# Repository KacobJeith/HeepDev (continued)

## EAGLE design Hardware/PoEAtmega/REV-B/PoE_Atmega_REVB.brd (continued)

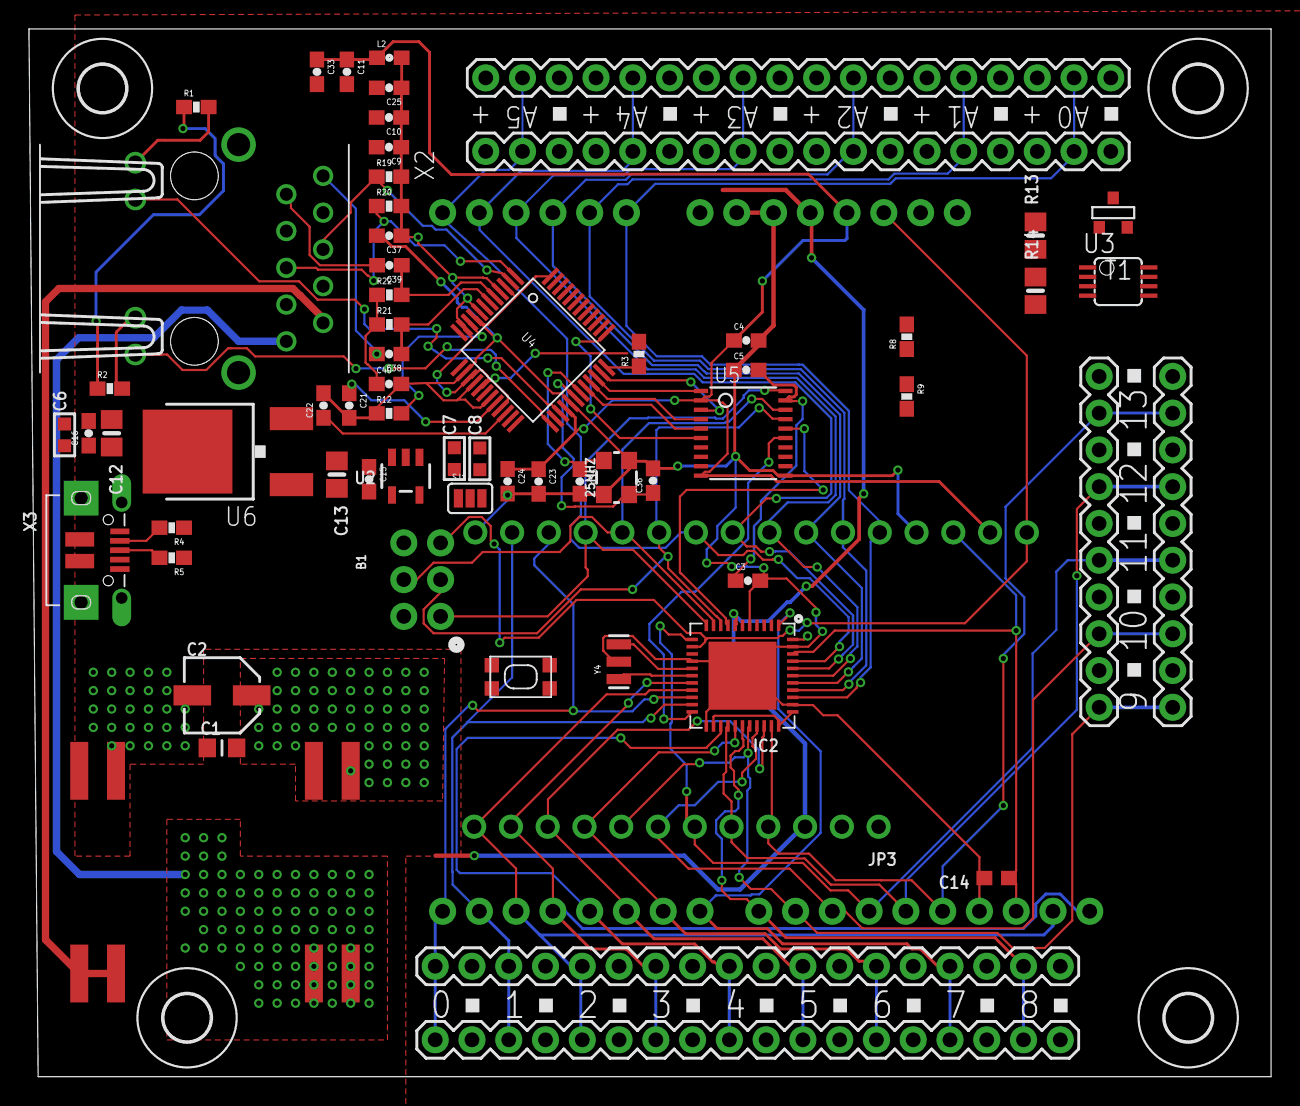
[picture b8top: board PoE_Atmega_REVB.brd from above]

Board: 2 copper layers, 85.8 x 72.4 mm, 70 parts (1 on the bottom side), 66 nets.

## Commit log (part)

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2018-04-10 HEEP-953 added the icons and canonical link to redirect http to https
2018-04-10 HEEP-952 dynamically import the landing page, reduces the critical loading path resource size by factor of 2
2018-04-10 HEEP-952 trying out some new babel modules to try to get dynamic importing to work
2018-04-10 HEEP-964 added logo
2018-04-10 HEEP-954 Landing, Store, and Checkout routes converted to lazy-loads. Some are unnecessary, but provide good example of how webpack and the browser work together to optimize resources
2018-04-10 HEEP-964 changed the way the logo loads in mobile vs. standard
2018-04-11 HEEP-964 fixed logo centering
2018-04-12 HEEP-949 updated to RS-274X (proper format for allpcb)
2018-04-12 HEEP-952 import specific icons instead of entire library
2018-04-12 HEEP-965 added gsap to package
2018-04-12 HEEP-951 fixed encoding issue when converting strings back into byte arrays. Wifi Reset works now
2018-04-13 HEEP-807 Only send the outputs
2018-04-13 HEEP-925 Added specifier to determine if WiFi
2018-04-13 HEEP-925 Calculate core memory correctly
2018-04-13 HEEP-927 upgrade .babelrc to the same that website is using, and remove unused npm modules
2018-04-13 HEEP-807 Added extra functions to express the many different ways to set a command and send data
2018-04-13 HEEP-960 use SVG for heep logo. Also adding missing svg for website
2018-04-13 HEEP-927 editing other pointers to assets to use the src/ path, and bringing back HMR on the dev server
2018-04-13 HEEP-963 the browser seems to have a cap on file size to store in localStorage, so at the moment the vendors bundle is not saving, but now that we understand how this works we are getting close
2018-04-16 HEEP-927 bump the electron version number
2018-04-16 HEEP-939 fixed reducer lazy loading for the database operations
2018-04-16 HEEP-937 display first and last name for avatar when on an account with no profile image
2018-04-16 HEEP-961 add reset device wifi button to the details panel and send command to device
2018-04-16 HEEP-965 deleted old dragging references
2018-04-16 HEEP-924 add zoom in and zoom out buttons to allow user to control zoom
2018-04-16 HEEP-924 pass scale to vertex calculations as well to correct calculations. move dragging into flowchart specific state tree
2018-04-16 HEEP-924 position fixed buttons on flowchart
2018-04-16 HEEP-965 added reducers for dragging
2018-04-16 HEEP-965 fixed range controllers
2018-04-17 HEEP-965 revamped draggable code and fixed range controllers
2018-04-17 HEEP-956 added a draggable scroll
2018-04-17 HEEP-924 set details to null on reloading of the flowchart. This helps with gsap initialization
2018-04-17 HEEP-956 added boundaries
2018-04-17 HEEP-768 Add designer control type to state
2018-04-17 HEEP-768 Protect from creating controls of type Select...
2018-04-17 HEEP-768 Removed word hardware from function
2018-04-17 HEEP-768 Functionalized write function code
2018-04-17 HEEP-956 it worksnpm run devnpm run devnpm run devnpm run devnpm run devnpm run dev set some elegant bounds on draggable
2018-04-17 HEEP-768 Now immediately return state instead of wrapping code in curly braces
2018-04-17 HEEP-956 successfully save positions and fixed bounds
2018-04-18 HEEP-965 fixed draggable, scrollbars, and weird window sizing
2018-04-18 HEEP-988 nullify details panel on mount
2018-04-18 HEEP-990 remove service worker from Electron App - it isn't necessary
2018-04-19 HEEP-969 fix app bar logo dependency
2018-04-19 HEEP-766 Added raw loader back in so that ino file could be imported as string by webpack
2018-04-19 HEEP-766 Added reducer for application name selection
2018-04-19 HEEP-991 remove unused dependency
2018-04-20 HEEP-969 remove auth, user profile, and developer routes for soft launch. Going with comment-out strategy so that we aren't starting from scratch for the DIY store
2018-04-20 HEEP-766 Hide controls on non custom application
2018-04-20 HEEP-969 add Industry routes to desktop and mobile appbar
2018-04-20 HEEP-766 Write out custom app ino file
2018-04-20 HEEP-766 use real climate ino file
2018-04-20 HEEP-766 Can now download all real ino files
2018-04-20 HEEP-923 added contactform.js
2018-04-21 HEEP-994 deleting the body block
2018-04-23 HEEP-766 Build and Buildfast now call get examples script
2018-04-23 HEEP-766 Made application dictionary into one array
2018-04-23 HEEP-923 added mobile compatibility and map
2018-04-23 HEEP-969 expand overlay to full width
2018-04-24 HEEP-923 changed tagline
2018-04-24 HEEP-1001 added state for collapsed device
2018-04-24 HEEP-1001 added icons in
2018-04-24 HEEP-1001 implemented collapsible
2018-04-24 HEEP-1004 tweaked language
2018-04-25 HEEP-1001 working collapse with smooth animation
2018-04-25 HEEP-966 Added a function to find generic MOPs from device memory
2018-04-25 HEEP-966 Added processed device ID to user MOP
2018-04-25 HEEP-1006 added new svg and fixed button type
2018-04-25 HEEP-969 functionalize sections, add some pictures, add a link to the contact page
2018-04-26 HEEP-969 tweak Security language, add more info link option to sections
2018-04-26 HEEP-969 tweak language
2018-04-26 HEEP-969 remove redundant sentence
2018-04-26 HEEP-1001 moved controlknobs to new component, messed with device grid
2018-04-26 HEEP-966 Finalized user MOP Test
2018-04-26 HEEP-986 sticking a commit with correct issue ID on the end
2018-04-26 HEEP-1001 added new ControlKnob component
2018-04-26 HEEP-1001 removed controlknob file
2018-04-26 HEEP-1001 fixed the inactive vertex color
2018-04-27 HEEP-607 Pass high low values into control setting functions
2018-04-27 HEEP-607 Made set val test compatible with new style of set val
2018-04-27 HEEP-607 Tested byte counter within setval execution
2018-04-27 HEEP-607 Added a new edge case test
2018-04-27 HEEP-1001 tidied up some stuff
2018-04-27 HEEP-1001 moved buttons back
2018-04-27 HEEP-1001 changed from iconbutton to button
2018-04-27 HEEP-1001 fixed margins and padding on grids
2018-04-27 HEEP-1001 fixed padding on titlecontainer
2018-04-27 HEEP-1001 fixed opacity issues for device details on collapse
2018-04-27 HEEP-1001 fixed icon colors
2018-04-27 HEEP-693 Handle control names with spaces
2018-04-27 HEEP-1007 handle mobile for the split section cards - always put the image first followed by the rich content
2018-04-27 HEEP-1007 move the PaperSignals movie to firebase
2018-04-30 HEEP-875 Tested get IP From memory function
2018-04-30 HEEP-983 made some changes to the reducers and actions
2018-04-30 HEEP-1007 add a page for commercial case studies
2018-04-30 HEEP-989 css hell is winning, fixed added another div for bounds
2018-04-30 HEEP-999 data now makes it from the form to the firebase function
2018-04-30 HEEP-999 validate form inputs on the Contact Page
2018-05-01 HEEP-875 Made vertex modify in place with new IP Address
2018-05-02 HEEP-875 Created broadcast and get IP functions in heepcomms
2018-05-02 HEEP-875 Handle IP Change has a ROP now
2018-05-04 HEEP-983 add a button on the flowchart to trigger save state
2018-05-04 HEEP-1008 made changes to typography
2018-05-04 HEEP-1008 deleted references to custom loading
2018-05-07 HEEP-983 handled case where one of the snapshot devices is not presently visible on the frontend
2018-05-07 HEEP-1018 added container heights to access point and setting pages
2018-05-07 HEEP_1020 fixed appbar resizing breakpoints
2018-05-07 HEEP-1020 fixed gradient logo
2018-05-07 HEEP-1020 changed appbar font type to oswald
2018-05-07 HEEP-1021 fix vertex updating render madness
2018-05-08 HEEP-1021 clean up comments
2018-05-08 HEEP-1021 remove unused position logic from heep serverside parser
2018-05-08 HEEP-1021 prevent complete app refresh on device card positioning
2018-05-08 HEEP-1022 changed the colors of the graphics
2018-05-08 HEEP-1022 added images to the mission and our story
2018-05-08 HEEP-1022 changed founders images to black and white, made other stuff more colorful
2018-05-09 HEEP-1023 added css stylesheet
2018-05-09 HEEP-1023 added index css file
2018-05-09 HEEP-1026 HEEP-1027 add privacy policy and terms of service to website from shopify
2018-05-09 HEEP-1027 fixed stretch formatting, removed unused raw loaded i previously added
2018-05-09 HEEP-1030 added pictures, fixed colors
2018-05-10 HEEP-1030 added gradient to about page, changed title
2018-05-10 HEEP-1029 remove unused links from footer
2018-05-10 HEEP-1031 fixed appbar buttons
2018-05-10 HEEP-1032 log page views from all active pages
2018-05-10 HEEP-1033 A Series of socket stabilizations for ROP handling
2018-05-11 HEEP-1035 render the controls even when the controlStructure has not been set by the server
2018-05-11 HEEP-1035 all behavior is as expected now. But...devices will continue to be discovered in perpetuity until you fully flush your flowchart space
2018-05-11 HEEP-1035 remove the controlStructure from the default redux tree and the server logic
2018-05-11 HEEP-926 successful vertex rendering
2018-05-11 HEEP-1036 cut the more consumer intended cards on the about us page
2018-05-11 HEEP-926 tested draggable hittest but will need to write own function
2018-05-13 HEEP-1046 Initial commit for Rev-G (stability)
2018-05-13 HEEP-1046 Improved heat dissapation on Wiznet
2018-05-13 HEEP-1046 added analog terminal blocks to schematic
2018-05-13 HEEP-1046 extended southside
2018-05-14 HEEP-1046 stopping for the night to focus on JW
2018-05-14 HEEP-1046 allowed for more ground plane @ ethernet jack
2018-05-14 HEEP-926 successfully drops on another input!
2018-05-15 HEEP-1049 Adding HowItWorks.js in place of current landing page
2018-05-15 HEEP-1046 dylan approved, init bom csv
2018-05-15 HEEP-926 rename redux state
2018-05-15 HEEP-1035 fix a bug causing errors in the details panel
2018-05-16 HEEP-926 separated out draggablevertex
2018-05-16 HEEP-926 reducer bad boii
2018-05-16 HEEP-1042 fix serverside vertice deletion logic
2018-05-16 HEEP-1042 set build version 0.1.9
2018-05-16 HEEP-1042 log new vertex with initialized timeSinceDiscovered
2018-05-17 HEEP-926 moved selectedoutput to root
2018-05-21 HEEP-1011 Fixed dumb typo that was blocking pinMode in device designer
2018-05-21 HEEP-1017 Handle get control value for momentary inputs
2018-05-21 HEEP-1017 Added set control value logic
2018-05-21 HEEP-1017 Fixed momentary control setting
2018-05-22 HEEP-1044 handle edge cases on values
2018-05-22 HEEP-1044 push x to the left so that it can be seen
2018-05-22 HEEP-1058 tweakz
2018-05-23 HEEP-926 fixed vertex reducer
2018-05-23 HEEP-1059 map control to device structure on serverside interp retation and save to device
2018-05-24 HEEP_926 fixed everything
2018-05-25 HEEP-926 deleted console logs
2018-05-25 HEEP-926 fixed vertex path code
2018-05-25 HEEP-1041 editted reducer so that controls are not updated when dragging in livemode
2018-05-27 HEEP-1052 implement deletion
2018-05-28 HEEP-1012 added overflow hiddens
2018-05-28 HEEP-1012 removed overflow hidden from pagecontainer
2018-05-29 HEEP-1052 handle case when receiving control and its context is not available
2018-05-31 HEEP-1049 tweaked more copy, removed DIY / Maker page and links from app bar
2018-06-01 HEEP-1049 made tweaks
2018-06-13 HEEP-1084 added lock state to reducer
2018-06-13 HEEP-1085 add a visibility button for toggling vertex visibility
2018-06-14 HEEP-1085 allow vertex visibility in all lock states
2018-06-14 HEEP-1084 added lock to range controls
2018-06-14 HEEP-1085 larger range control pucks
2018-06-14 HEEP-1085 make the vertex knobs way more subtle when the visibility is toggled off
2018-06-14 HEEP-1086 resize the control icons in the details panel to be sized properly
2018-07-25 HEEP-1105 Initial functioning PATCH method
2018-07-25 HEEP-1105 Now sends controls to firestore properly
2018-07-25 HEEP-1105 Fixed name context adding
2018-07-27 HEEP-1093 Real time captured from firebase function
2018-07-27 HEEP-1093 Real Time ESP Analytics
